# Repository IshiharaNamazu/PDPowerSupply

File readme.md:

ギターエフェクター用のパワーサプライ
USB PD充電器 / DC Jackで給電可
9V3A MAX，出力6ポート
5Aのポリスイッチ，12Vのツェナー付き

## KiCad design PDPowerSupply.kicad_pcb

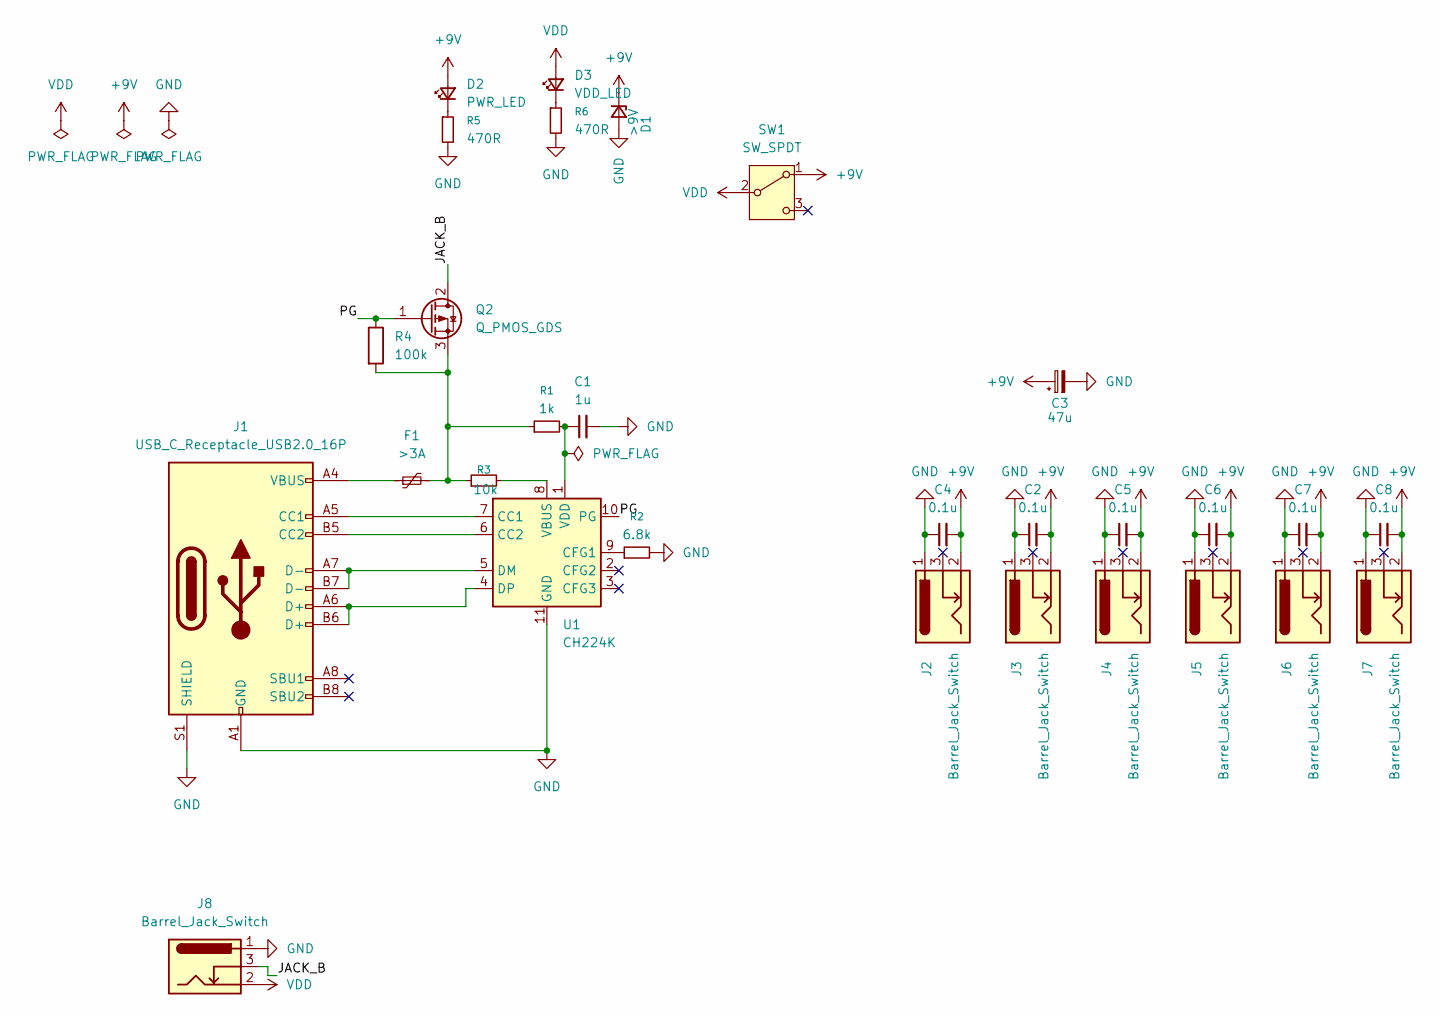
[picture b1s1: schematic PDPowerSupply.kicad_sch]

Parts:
C1: 1u; C_0603_1608Metric_Pad1.08x0.95mm_HandSolder
C2, C4, C5, C6, C7, C8: 0.1u; C_0603_1608Metric_Pad1.08x0.95mm_HandSolder
C3: 47u; CP_Radial_D5.0mm_P2.00mm
D1: >9V; D_TUMD2
D2: PWR_LED; LED_0603_1608Metric_Pad1.05x0.95mm_HandSolder
D3: VDD_LED; LED_0603_1608Metric_Pad1.05x0.95mm_HandSolder
F1: >3A; Fuse_Bourns_MF-RG300
J1: USB_C_Receptacle_USB2.0_16P; USB_C_Receptacle_GCT_USB4105-xx-A_16P_TopMnt_Horizontal
J2, J3, J4, J5, J6, J7, J8: Barrel_Jack_Switch; BarrelJack_Horizontal
Q2: Q_PMOS_GDS; TO-251-3_Vertical
R1: 1k; C_0603_1608Metric_Pad1.08x0.95mm_HandSolder
R2: 6.8k; C_0603_1608Metric_Pad1.08x0.95mm_HandSolder
R3: 10k; C_0603_1608Metric_Pad1.08x0.95mm_HandSolder
R4: 100k; C_0603_1608Metric_Pad1.08x0.95mm_HandSolder
R5, R6: 470R; C_0603_1608Metric_Pad1.08x0.95mm_HandSolder
SW1: SW_SPDT; ROCKERSW_3MS1J102M2QES
U1: CH224K; SSOP-10-1EP_3.9x4.9mm_P1mm_EP2.1x3.3mm

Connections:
+9V: C2.2, C3.1, C4.2, C5.2, C6.2, C7.2, C8.2, D1.1 (K), D2.2 (A), J2.2, J3.2, J4.2, J5.2, J6.2, J7.2, SW1.1 (A)
/JACK_B: J8.3, Q2.2 (D)
/PG: Q2.1 (G), R4.1, U1.10 (PG)
GND: C1.2, C2.1, C3.2, C4.1, C5.1, C6.1, C7.1, C8.1, D1.2 (A), J1.A1 (GND), J1.A12 (GND), J1.B1 (GND), J1.B12 (GND), J1.S1 (SHIELD), J2.1, J3.1, J4.1, J5.1, J6.1, J7.1, J8.1, R2.2, R5.2, R6.2, U1.11 (GND)
unnamed: D2.1 (K), R5.1
unnamed: D3.1 (K), R6.1
unnamed: F1.1, J1.A4 (VBUS), J1.A9 (VBUS), J1.B4 (VBUS), J1.B9 (VBUS)
unnamed: J1.A5 (CC1), U1.7 (CC1)
unnamed: J1.B5 (CC2), U1.6 (CC2)
unnamed: F1.2, Q2.3 (S), R1.1, R3.1, R4.2
unnamed: R2.1, U1.9 (CFG1)
unnamed: J1.A7 (D-), J1.B7 (D-), U1.5 (DM)
unnamed: J1.A6 (D+), J1.B6 (D+), U1.4 (DP)
unnamed: R3.2, U1.8 (VBUS)
unnamed: C1.1, R1.2, U1.1 (VDD)
VDD: D3.2 (A), J8.2, SW1.2 (B)

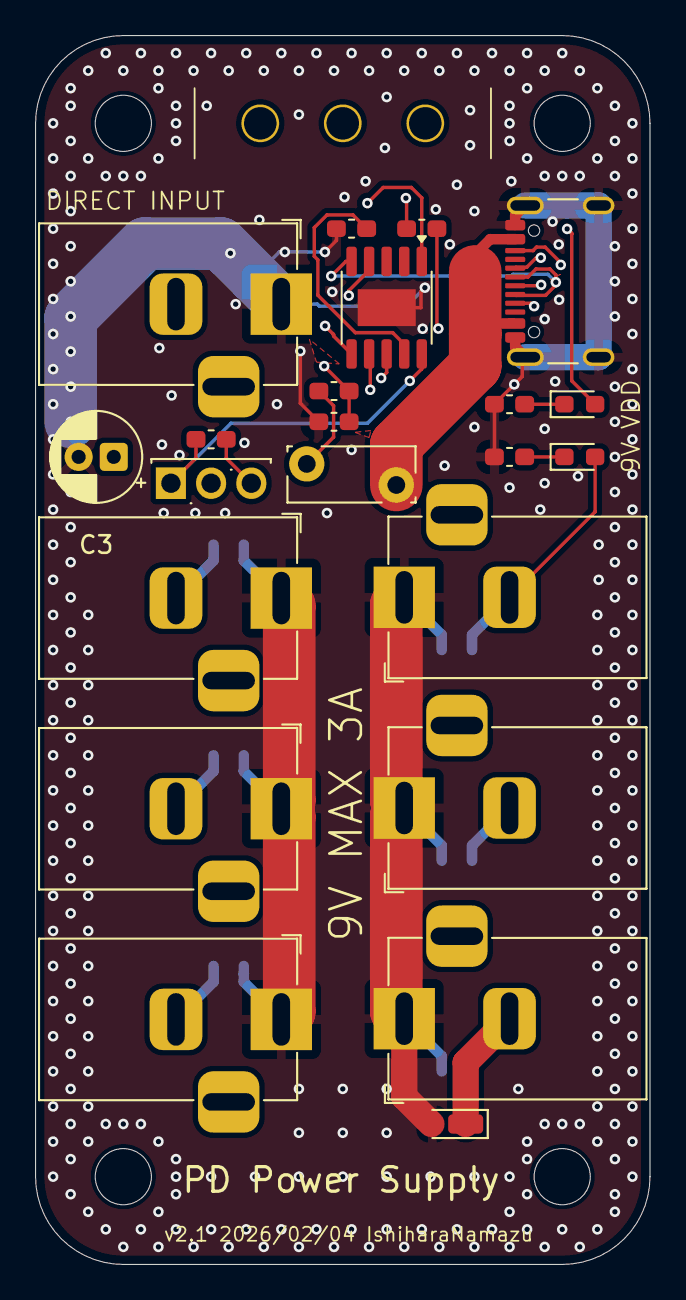
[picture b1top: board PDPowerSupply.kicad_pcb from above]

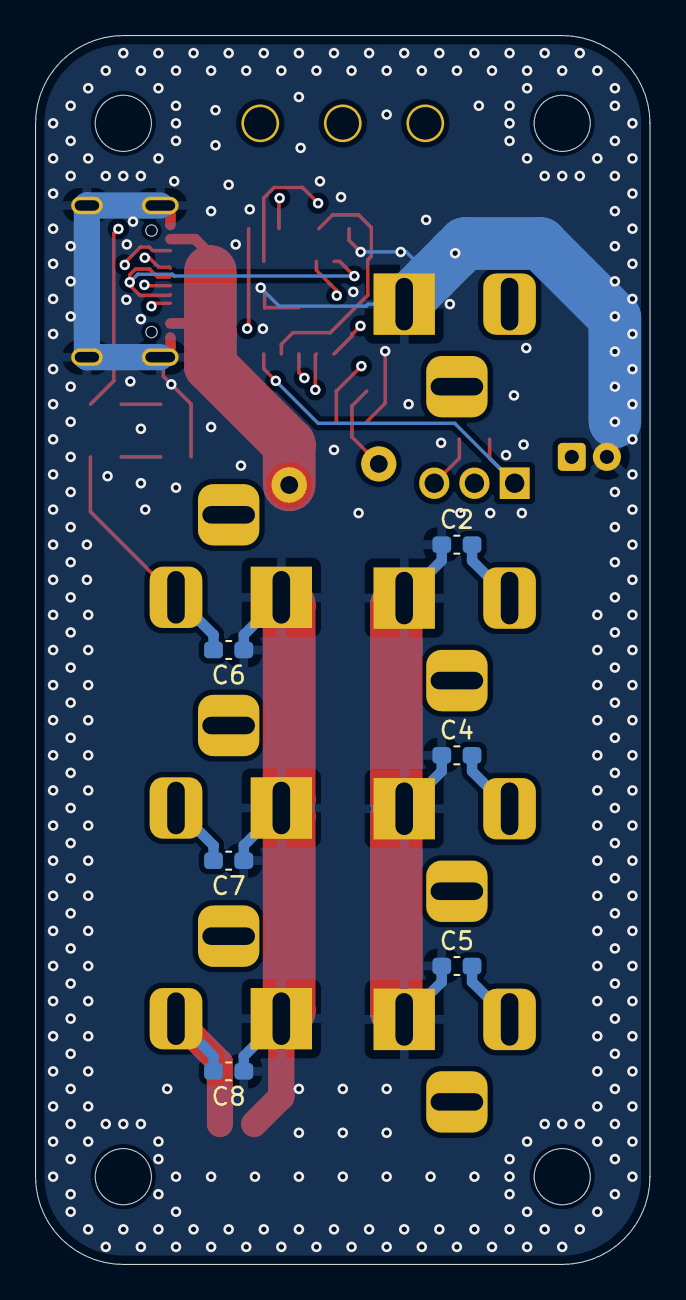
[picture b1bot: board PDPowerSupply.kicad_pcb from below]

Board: 4 copper layers, 35.0 x 70.0 mm, 33 parts (6 on the bottom side), 16 nets.

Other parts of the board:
REF1, REF2, REF3, REF4: MountingHole_3.2mm_M3

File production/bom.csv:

Designator,Footprint,Quantity,Value,LCSC Part #
C1,0603,1,1u,
"C2, C4, C5, C6, C7, C8",0603,6,0.1u,
C3,CP_Radial_D5.0mm_P2.00mm,1,47u,
D1,D_TUMD2,1,>9V,
D2,0603,1,PWR_LED,
D3,0603,1,VDD_LED,
F1,Fuse_Bourns_MF-RG300,1,>3A,
J1,USB_C_Receptacle_GCT_USB4105-xx-A_16P_TopMnt_Horizontal,1,USB_C_Receptacle_USB2.0_16P,
"J2, J3, J4, J5, J6, J7, J8",BarrelJack_Horizontal,7,Barrel_Jack_Switch,
Q2,TO-251-3_Vertical,1,Q_PMOS_GDS,
R1,0603,1,1k,
R2,0603,1,6.8k,
R3,0603,1,10k,
R4,0603,1,100k,
"R5, R6",0603,2,470R,
SW1,ROCKERSW_3MS1J102M2QES,1,SW_SPDT,
U1,SSOP-10-1EP_3.9x4.9mm_P1mm_EP2.1x3.3mm,1,CH224K,

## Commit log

2026-01-25 v1.0作った，修正点記載
2026-02-25 v2.0発注
2026-02-25 v2.1 シルク追加
